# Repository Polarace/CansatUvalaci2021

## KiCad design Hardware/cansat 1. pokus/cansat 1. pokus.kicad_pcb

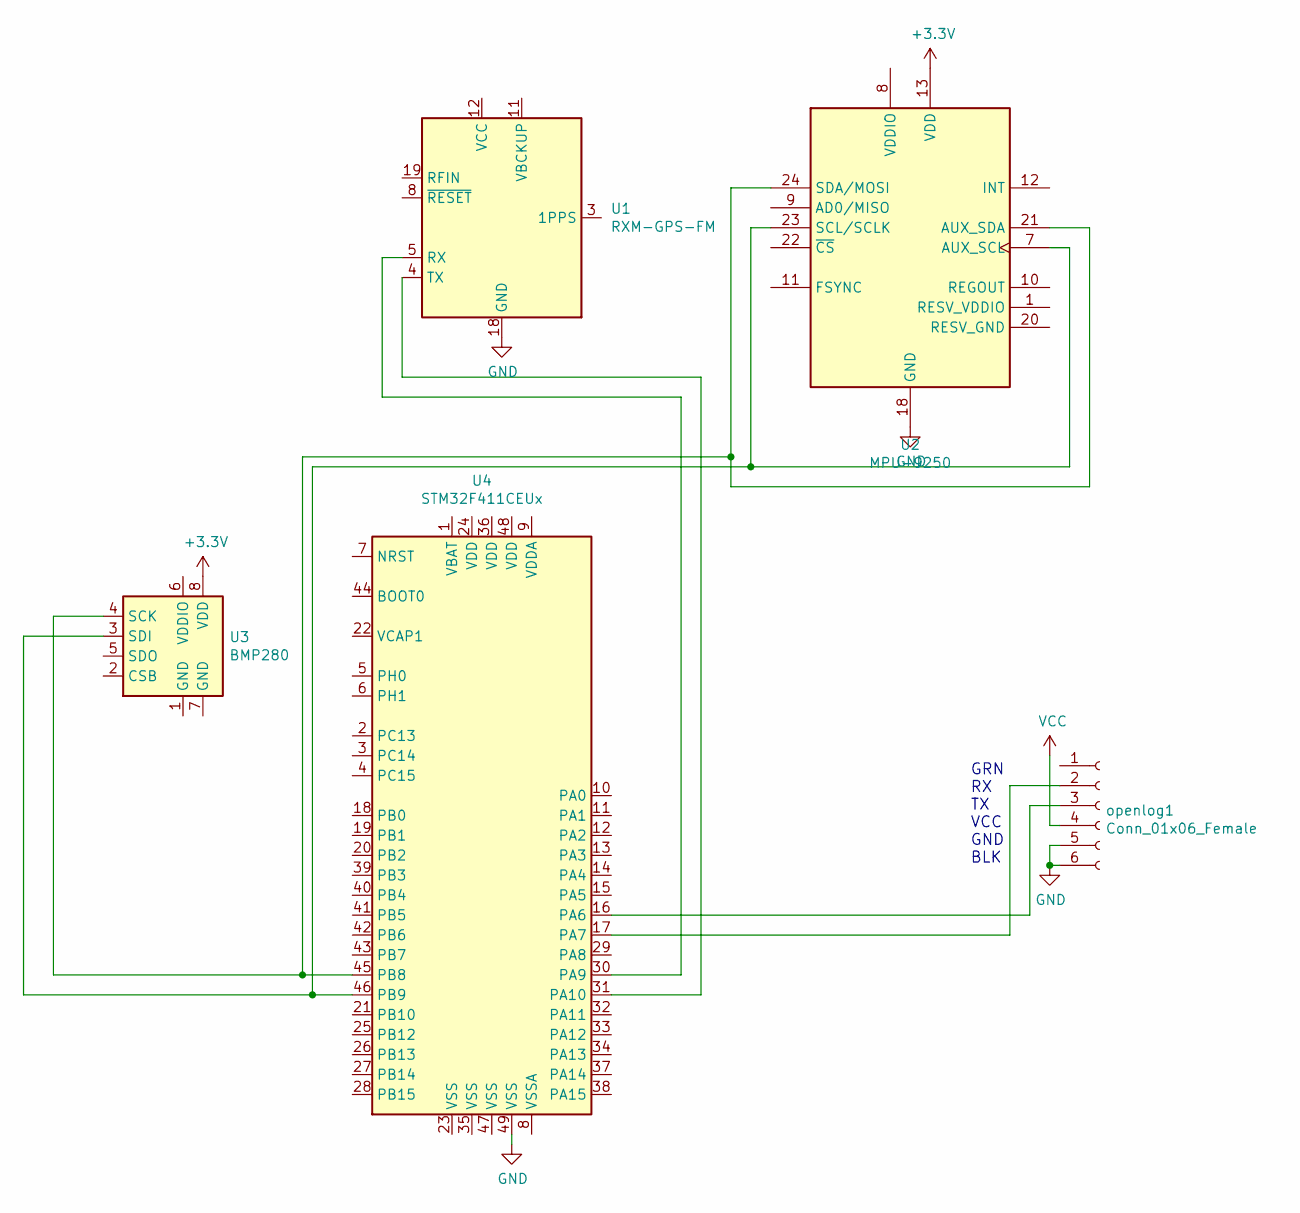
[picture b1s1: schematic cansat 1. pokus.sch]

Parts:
U1: RXM-GPS-FM; Linx_RXM-GPS
U2: MPU-9250; InvenSense_QFN-24_3x3mm_P0.4mm
U3: BMP280; Bosch_LGA-8_2x2.5mm_P0.65mm_ClockwisePinNumbering
U4: STM32F411CEUx; QFN-48-1EP_7x7mm_P0.5mm_EP5.6x5.6mm
openlog1: Conn_01x06_Female; PinSocket_1x06_P2.54mm_Vertical

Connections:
+3V3: U2.13 (VDD), U3.8 (VDD)
GND: U1.18 (GND), U1.20 (GND), U1.21 (GND), U1.22 (GND), U2.18 (GND), U4.49 (VSS), openlog1.5, openlog1.6
unnamed: U1.4 (TX), U4.31 (PA10)
unnamed: U1.5 (RX), U4.30 (PA9)
unnamed: U2.21 (AUX_SDA), U2.24 (SDA/MOSI), U3.4 (SCK), U4.45 (PB8)
unnamed: U2.7 (AUX_SCL), U2.23 (SCL/SCLK), U3.3 (SDI), U4.46 (PB9)
unnamed: U4.16 (PA6), openlog1.3
unnamed: U4.17 (PA7), openlog1.2
VCC: openlog1.4

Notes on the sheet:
GRN RX TX VCC GND BLK

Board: 2 copper layers, 5 parts (0 on the bottom side), 8 nets, no tracks yet.

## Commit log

2021-06-16 Init
2021-06-16 Added basestation code
2021-06-16 Cleanup
2021-06-22 pre semifinals push
2021-06-28 Added rover test software
2021-06-28 Motor driver library
    Added motor driver library support for Arduino IDE
2021-07-10 added testing code
2021-08-15 Primary mission progress
2022-03-16 asd
    asadada
